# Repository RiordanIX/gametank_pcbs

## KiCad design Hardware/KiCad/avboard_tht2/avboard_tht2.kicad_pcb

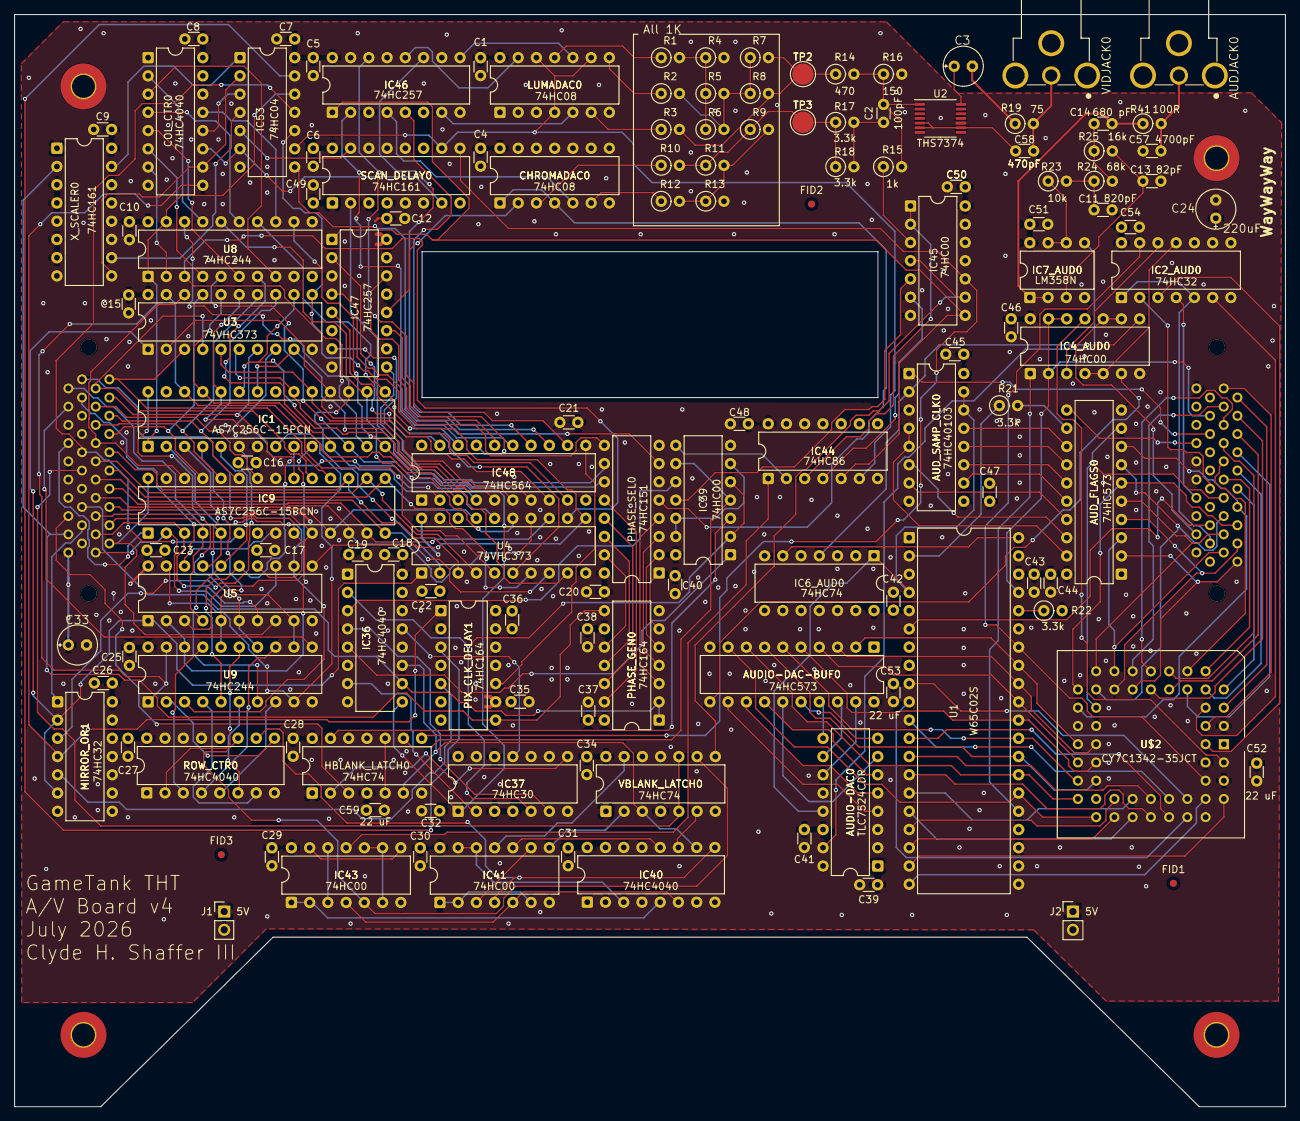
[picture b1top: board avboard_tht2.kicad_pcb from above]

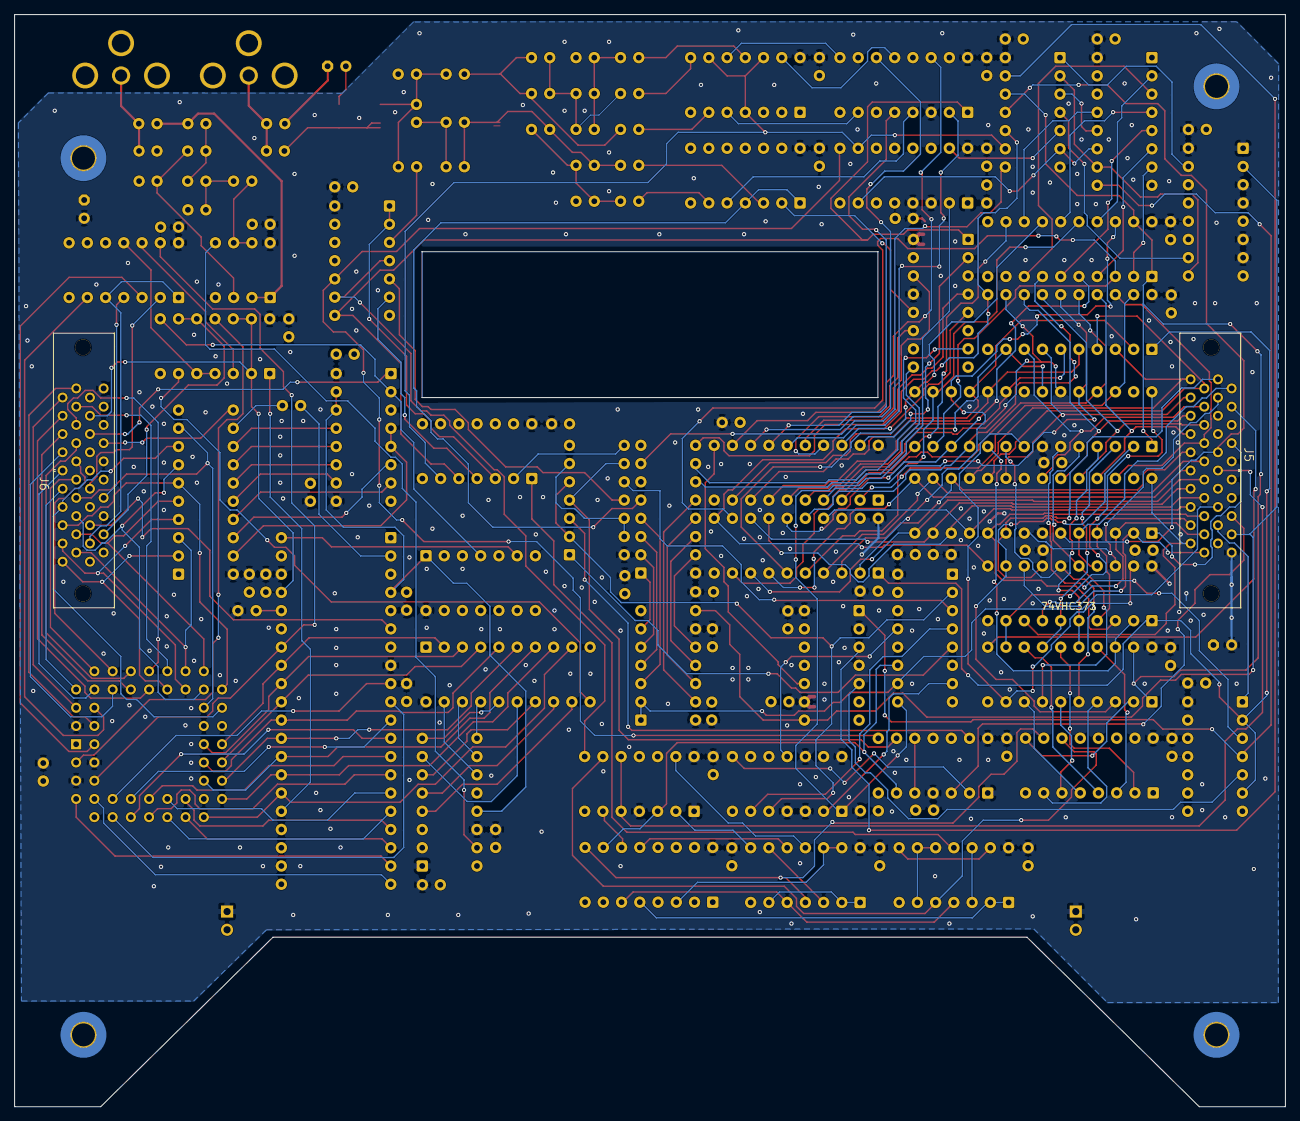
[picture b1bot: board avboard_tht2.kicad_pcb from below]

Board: 4 copper layers, 177.0 x 152.1 mm, 139 parts (2 on the bottom side), 246 nets.

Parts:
AUDIO-DAC0: TLC7524CDR; DIP-16_W7.62mm
AUDIO-DAC-BUF0: 74HC573; DIP-20_W7.62mm
AUDJACK0: RCJ-013; CUI_RCJ-014
AUD_FLAGS0: 74HC573; DIP-20_W7.62mm
AUD_SAMP_CLK0: 74HC40103; DIP-16_W7.62mm
C1, C4, C5, C6, C7, C8, C9, C10, C12, C15, C16, C17, C18, C19, C20, C21, C22, C23, C25, C26, C27, C28, C29, C30, C31, C32, C34, C35, C36, C37, C38, C39, C40, C41, C42, C43, C44, C45, C46, C47, C48, C49, C50, C51, C54: 100 nF; C_Disc_D3.0mm_W1.6mm_P2.50mm
C2: 100pF; C_Disc_D3.0mm_W1.6mm_P2.50mm
C3, C24, C33: 220uF; E2,5-6E
C11: 820pF; C_Disc_D3.0mm_W1.6mm_P2.50mm
C13: 82pF; C_Disc_D3.0mm_W1.6mm_P2.50mm
C14: 680 pF; C_Disc_D3.0mm_W1.6mm_P2.50mm
C52, C53, C59: 22 uF; C_Disc_D3.0mm_W1.6mm_P2.50mm
C57: 4700pF; C_Disc_D3.0mm_W1.6mm_P2.50mm
C58: 470pF; C_Disc_D3.0mm_W1.6mm_P2.50mm
CHROMADAC0: 74HC08; DIP-14_W7.62mm
COL_CTR0: 74HC4040; DIP-16_W7.62mm
FID1, FID2, FID3: Fiducial; Fiducial_1mm_Mask2mm
H1, H2, H3, H4: MountingHole_Pad; MountingHole_3.2mm_M3_Pad_TopBottom
HBLANK_LATCH0: 74HC74; DIP-14_W7.62mm
IC1, IC9: AS7C256C-15PCN; DIP-28_W7.62mm
IC2_AUD0: 74HC32; DIP-14_W7.62mm
IC4_AUD0, IC39, IC41, IC43, IC45: 74HC00; DIP-14_W7.62mm
IC6_AUD0: 74HC74; DIP-14_W7.62mm
IC7_AUD0: LM358N; DIP-8_W7.62mm
IC36, IC40: 74HC4040; DIP-16_W7.62mm
IC37: 74HC30; DIP-14_W7.62mm
IC44: 74HC86; DIP-14_W7.62mm
IC46, IC47: 74HC257; DIP-16_W7.62mm
IC48: 74HC564; DIP-20_W7.62mm
IC53: 74HC04; DIP-14_W7.62mm
J1, J2: 5V; PinHeader_1x02_P2.54mm_Vertical
J5: CON40_2X20_MU_TX24_JAE
J6: CON40_2X20_MU_TX25_JAE
LUMADAC0: 74HC08; DIP-14_W7.62mm
MIRROR_OR1: 74HC32; DIP-14_W7.62mm
PHASE_GEN0: 74HC164; DIP-14_W7.62mm
PHASE_SEL0: 74HC151; DIP-16_W7.62mm
PIX_CLK_DELAY1: 74HC164; DIP-14_W7.62mm
R1, R2, R3, R4, R5, R6, R7, R8, R9, R10, R11, R12, R13, R15: 1k; R_Axial_DIN0207_L6.3mm_D2.5mm_P2.54mm_Vertical
R14: 470; R_Axial_DIN0207_L6.3mm_D2.5mm_P2.54mm_Vertical
R16: 150; R_Axial_DIN0207_L6.3mm_D2.5mm_P2.54mm_Vertical
R17, R18, R21, R22: 3.3k; R_Axial_DIN0207_L6.3mm_D2.5mm_P2.54mm_Vertical
R19: 75; R_Axial_DIN0207_L6.3mm_D2.5mm_P2.54mm_Vertical
R23: 10k; R_Axial_DIN0207_L6.3mm_D2.5mm_P2.54mm_Vertical
R24: 68k; R_Axial_DIN0207_L6.3mm_D2.5mm_P2.54mm_Vertical
R25: 16k; R_Axial_DIN0207_L6.3mm_D2.5mm_P2.54mm_Vertical
R41: 100R; R_Axial_DIN0207_L6.3mm_D2.5mm_P2.54mm_Vertical
ROW_CTR0: 74HC4040; DIP-16_W7.62mm
SCAN_DELAY0: 74HC161; DIP-16_W7.62mm
TP2, TP3: TestPoint_Pad_D3.0mm
U1: W65C02S; DIP-40_W15.24mm
U2: THS7374; TSSOP-14_4.4x5mm_P0.65mm
U3, U4, U5: 74VHC373; DIP-20_W7.62mm
U8, U9: 74HC244; DIP-20_W7.62mm
U$2: CY7C1342-35JCT; PLCC-52_THT-Socket
VBLANK_LATCH0: 74HC74; DIP-14_W7.62mm
VIDJACK0: COMPOSITE; CUI_RCJ-014
X_SCALER0: 74HC161; DIP-16_W7.62mm

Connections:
/Audio Coprocessor/AA0: U1.9 (A0), U$2.45 (AR0)
/Audio Coprocessor/AA1: U1.10 (A1), U$2.44 (AR1)
/Audio Coprocessor/AA2: U1.11 (A2), U$2.43 (AR2)
/Audio Coprocessor/AA3: U1.12 (A3), U$2.42 (AR3)
/Audio Coprocessor/AA4: U1.13 (A4), U$2.41 (AR4)
/Audio Coprocessor/AA5: U1.14 (A5), U$2.40 (AR5)
/Audio Coprocessor/AA6: U1.15 (A6), U$2.39 (AR6)
/Audio Coprocessor/AA7: U1.16 (A7), U$2.38 (AR7)
/Audio Coprocessor/AA8: U1.17 (A8), U$2.37 (AR8)
/Audio Coprocessor/AA9: U1.18 (A9), U$2.36 (AR9)
/Audio Coprocessor/AA10: U1.19 (A10), U$2.47 (AR10)
/Audio Coprocessor/AA11: U1.20 (A11), U$2.48 (AR11)
/Audio Coprocessor/AA15: IC4_AUD0.1 (I0), U1.25 (A15)
/Audio Coprocessor/AD0: AUDIO-DAC-BUF0.2 (1D), U1.33 (D0), U$2.27 (DR0)
/Audio Coprocessor/AD1: AUDIO-DAC-BUF0.3 (2D), U1.32 (D1), U$2.28 (DR1)
/Audio Coprocessor/AD2: AUDIO-DAC-BUF0.4 (3D), U1.31 (D2), U$2.29 (DR2)
/Audio Coprocessor/AD3: AUDIO-DAC-BUF0.5 (4D), U1.30 (D3), U$2.30 (DR3)
/Audio Coprocessor/AD4: AUDIO-DAC-BUF0.6 (5D), U1.29 (D4), U$2.31 (DR4)
/Audio Coprocessor/AD5: AUDIO-DAC-BUF0.7 (6D), U1.28 (D5), U$2.32 (DR5)
/Audio Coprocessor/AD6: AUDIO-DAC-BUF0.8 (7D), U1.27 (D6), U$2.33 (DR6)
/Audio Coprocessor/AD7: AUDIO-DAC-BUF0.9 (8D), U1.26 (D7), U$2.34 (DR7)
/Audio Coprocessor/AR/~WB: IC2_AUD0.13 (I1), U1.34 (R/WB), U$2.50 (R/_WR)
/Audio Coprocessor/AUDIO_RDY: AUD_FLAGS0.12 (8Q), R21.2
/Audio Coprocessor/AUD_REG0: IC4_AUD0.9 (I0), IC4_AUD0.10 (I1), J6.17
/Audio Coprocessor/AUD_REG6: AUD_FLAGS0.11 (C), J6.7
/Audio Coprocessor/CLK3_5_AUD: AUD_SAMP_CLK0.1 (CP), J6.6
/Audio Coprocessor/CLK14_AUD: IC4_AUD0.2 (I1), IC4_AUD0.12 (I0), IC4_AUD0.13 (I1), J6.4, U1.37 (PH0-IN)
/Audio Coprocessor/DAC_SELECT: AUDIO-DAC-BUF0.11 (C), IC4_AUD0.6 (O)
/Audio Coprocessor/SysA0: J6.32, U$2.7 (AL0)
/Audio Coprocessor/SysA1: J6.31, U$2.8 (AL1)
/Audio Coprocessor/SysA2: J6.30, U$2.9 (AL2)
/Audio Coprocessor/SysA3: J6.29, U$2.10 (AL3)
/Audio Coprocessor/SysA4: J6.28, U$2.11 (AL4)
/Audio Coprocessor/SysA5: J6.27, U$2.12 (AL5)
/Audio Coprocessor/SysA6: J6.26, U$2.13 (AL6)
/Audio Coprocessor/SysA7: J6.25, U$2.14 (AL7)
/Audio Coprocessor/SysA8: J6.24, U$2.15 (AL8)
/Audio Coprocessor/SysA9: J6.23, U$2.16 (AL9)
/Audio Coprocessor/SysA10: J6.22, U$2.5 (AL10)
/Audio Coprocessor/SysA11: J6.21, U$2.4 (AL11)
/Audio Coprocessor/SysD0: AUD_FLAGS0.2 (1D), J6.40, U$2.17 (DL0)
/Audio Coprocessor/SysD1: AUD_FLAGS0.3 (2D), J6.39, U$2.18 (DL1)
/Audio Coprocessor/SysD2: AUD_FLAGS0.4 (3D), J6.38, U$2.19 (DL2)
/Audio Coprocessor/SysD3: AUD_FLAGS0.5 (4D), J6.37, U$2.20 (DL3)
/Audio Coprocessor/SysD4: AUD_FLAGS0.6 (5D), J6.36, U$2.21 (DL4)
/Audio Coprocessor/SysD5: AUD_FLAGS0.7 (6D), J6.35, U$2.22 (DL5)
/Audio Coprocessor/SysD6: AUD_FLAGS0.8 (7D), J6.34, U$2.23 (DL6)
/Audio Coprocessor/SysD7: AUD_FLAGS0.9 (8D), J6.33, U$2.24 (DL7)
/Audio Coprocessor/~AUDIO_IRQ: AUDIO-DAC0.13 (~WR), AUD_SAMP_CLK0.14 (TC), AUD_SAMP_CLK0.15 (PE), IC6_AUD0.1 (CLR), U1.4 (IRQB)
/Audio Coprocessor/~AUDIO_NMI: J6.16, U1.6 (NMIB)
/Audio Coprocessor/~AUDIO_RESET: AUD_SAMP_CLK0.2 (MR), IC4_AUD0.8 (O), IC6_AUD0.4 (PRE)
/Audio Coprocessor/~RE2: IC2_AUD0.4 (I0), J6.13
/Audio Coprocessor/~WAV_SEL: IC2_AUD0.1 (I0), IC2_AUD0.5 (I1), J6.18
/Audio Coprocessor/~WE2: IC2_AUD0.2 (I1), J6.12
/Composite Video Generator/1V: IC40.9 (Q1), IC41.4 (I0), ROW_CTR0.10 (P1)
/Composite Video Generator/2H: IC36.9 (Q1), IC37.1 (I0), SCAN_DELAY0.2 (CLK)
/Composite Video Generator/4H: IC36.7 (Q2), IC37.2 (I1)
/Composite Video Generator/4V: IC40.6 (Q3), IC41.5 (I1), IC43.4 (I0)
/Composite Video Generator/8V: IC40.5 (Q4), IC43.1 (I0), IC43.2 (I1)
/Composite Video Generator/16H: IC36.5 (Q4), IC39.1 (I0)
/Composite Video Generator/16V: IC40.3 (Q5), IC41.12 (I0), IC41.13 (I1)
/Composite Video Generator/32H: IC36.3 (Q5), IC39.10 (I1)
/Composite Video Generator/64H: IC36.2 (Q6), IC37.5 (I4), IC39.2 (I1), IC39.5 (I1)
/Composite Video Generator/128H: IC36.4 (Q7), IC37.6 (I5)
/Composite Video Generator/256H: IC36.13 (Q8), IC37.11 (I6)
/Composite Video Generator/256V: IC40.12 (Q9), IC41.10 (I1)
/Composite Video Generator/BURST: IC44.5 (I1), IC45.8 (O), IC46.1 (~A/B), IC47.1 (~A/B)
/Composite Video Generator/CHROMACARRIER: R9.1, R10.2, R11.1, R17.1, R18.1, TP3.1 (1_1)
/Composite Video Generator/CLK3_5: IC36.10 (P1), J5.6, PHASE_GEN0.1 (A), PHASE_GEN0.2 (B)
/Composite Video Generator/CLK7: HBLANK_LATCH0.3 (CLK), J5.5
/Composite Video Generator/CLK14: J5.4, MIRROR_OR1.1 (I0)
/Composite Video Generator/CLK28: J5.3, PHASE_GEN0.8 (CLK), PIX_CLK_DELAY1.8 (CLK), X_SCALER0.2 (CLK)
/Composite Video Generator/CSYNC: IC45.3 (O), R15.1
/Composite Video Generator/HBLANK: HBLANK_LATCH0.9 (Q), IC39.4 (I0), IC39.9 (I0)
/Composite Video Generator/HRESET: HBLANK_LATCH0.6 (~Q), IC36.11 (RES), IC40.10 (P1), VBLANK_LATCH0.3 (CLK)
/Composite Video Generator/HUE0: IC47.9 (3Y), PHASE_SEL0.11 (A)
/Composite Video Generator/HUE1: IC47.7 (2Y), PHASE_SEL0.10 (B)
/Composite Video Generator/HUE2: IC47.4 (1Y), PHASE_SEL0.9 (C)
/Composite Video Generator/LUM0: IC46.12 (4Y), LUMADAC0.13 (I1)
/Composite Video Generator/LUM1: IC46.9 (3Y), LUMADAC0.10 (I1)
/Composite Video Generator/LUM2: IC46.7 (2Y), LUMADAC0.5 (I1)
/Composite Video Generator/LUMA: R3.2, R7.2, R8.2, R14.1, TP2.1 (1_1)
/Composite Video Generator/PICTURE-ENABLE: IC44.6 (O), IC53.9 (I), LUMADAC0.4 (I0), LUMADAC0.9 (I0), LUMADAC0.12 (I0), SCAN_DELAY0.10 (ENT)
/Composite Video Generator/PIXCLK: COL_CTR0.9 (Q1), MIRROR_OR1.4 (I0), PIX_CLK_DELAY1.1 (A)
/Composite Video Generator/PIXCLK_PhaseC: MIRROR_OR1.5 (I1), PIX_CLK_DELAY1.5 (QC)
/Composite Video Generator/PIXLATCH: IC48.11 (CLK), PIX_CLK_DELAY1.10 (QE)
/Composite Video Generator/PIXLOAD: IC53.13 (I), PIX_CLK_DELAY1.3 (QA)
/Composite Video Generator/ROW_COMPLETE: COL_CTR0.12 (Q9), IC53.3 (I)
/Composite Video Generator/SAT0: CHROMADAC0.5 (I1), IC46.4 (1Y)
/Composite Video Generator/SAT1: CHROMADAC0.2 (I1), IC47.12 (4Y)
/Composite Video Generator/VBLANK: IC43.5 (I1), ROW_CTR0.11 (RES), VBLANK_LATCH0.9 (Q)
/Composite Video Generator/VRESET: IC40.11 (RES), VBLANK_LATCH0.6 (~Q)
/Composite Video Generator/VWE: IC53.10 (O), U3.11 (LE), U4.11 (LE), U5.11 (LE)
/Composite Video Generator/XCLK: COL_CTR0.10 (P1), IC53.2 (O), X_SCALER0.9 (LD)
/Composite Video Generator/XRESET: COL_CTR0.11 (RES), IC53.6 (O), SCAN_DELAY0.7 (ENP)
/Composite Video Generator/~8V: IC43.3 (O), IC43.12 (I0)
/Composite Video Generator/~HBLANK: HBLANK_LATCH0.8 (~Q), IC45.10 (I1), SCAN_DELAY0.9 (LD)
/Composite Video Generator/~HRESET: HBLANK_LATCH0.5 (Q), HBLANK_LATCH0.10 (PRE)
/Composite Video Generator/~HSYNC: IC39.8 (O), IC44.2 (I1)
/Composite Video Generator/~MirrorLoad: MIRROR_OR1.2 (I1), MIRROR_OR1.6 (O), U3.1 (OE), U4.1 (OE), U5.1 (OE)
/Composite Video Generator/~MirrorWE: IC1.6 (~WE), MIRROR_OR1.3 (O)
/Composite Video Generator/~PICTURE-ENABLE: IC53.8 (O), PHASE_SEL0.7 (G)
/Composite Video Generator/~PIXLOAD: IC1.1 (~OE), IC53.12 (O), U8.1 (1OE), U8.19 (2OE), U9.1 (1OE), U9.19 (2OE)
/Composite Video Generator/~VBLANK: IC45.4 (I0), IC45.9 (I0), VBLANK_LATCH0.8 (~Q)
/Composite Video Generator/~VOE: IC9.1 (~OE), J5.13
/Composite Video Generator/~VRESET: J5.10, VBLANK_LATCH0.5 (Q), VBLANK_LATCH0.10 (PRE)
/Composite Video Generator/~VSYNC: IC43.11 (O), IC44.1 (I0)
/Composite Video Generator/~VWE: IC9.6 (~WE), IC53.11 (I), J5.12
GND: AUDIO-DAC0.2 (OUT2), AUDIO-DAC0.3 (GND), AUDIO-DAC0.12 (~CS), AUDIO-DAC-BUF0.1 (OC), AUDIO-DAC-BUF0.10 (GND), AUDJACK0.1A (1), AUDJACK0.1B (1), AUDJACK0.1C (1), AUD_FLAGS0.1 (OC), AUD_FLAGS0.10 (GND), AUD_SAMP_CLK0.3 (TE), AUD_SAMP_CLK0.8 (GND), C1.2, C4.2, C5.2, C6.2, C7.2, C8.2, C9.2, C10.2, C11.1, C12.2, C13.1, C15.2, C16.2, C17.2, C18.2, C19.2, C20.2, C21.2, C22.2, C23.2, C24.-, C25.2, C26.2, C27.2, C28.2, C29.2, C30.2, C31.2, C32.2, C33.-, C34.2, C35.2, C36.2, C37.2, C38.2, C39.2, C40.2, C41.2, C42.2, C43.2, C44.2, C45.2, C46.2, C47.2, C48.2, C49.2, C50.2, C51.2, C52.2, C53.2, C54.2, C57.2, C58.2, C59.2, CHROMADAC0.7 (GND), CHROMADAC0.9 (I0), CHROMADAC0.10 (I1), CHROMADAC0.12 (I0), CHROMADAC0.13 (I1), COL_CTR0.8 (VSS), H1.1 (1_1), H2.1 (1_1), H3.1 (1_1), H4.1 (1_1), HBLANK_LATCH0.7 (GND), HBLANK_LATCH0.11 (CLK), HBLANK_LATCH0.12 (D), IC1.21 (GND), IC1.27 (~CE), IC2_AUD0.7 (GND), IC4_AUD0.7 (GND), IC6_AUD0.3 (CLK), IC6_AUD0.7 (GND), IC7_AUD0.4 (V-), IC9.21 (GND), IC9.27 (~CE), IC36.8 (VSS), IC37.7 (GND), IC39.7 (GND), IC40.8 (VSS), IC41.7 (GND), IC43.7 (GND), IC44.7 (GND), IC45.7 (GND), IC46.6 (2B), IC46.8 (GND), IC46.10 (3B), IC46.13 (4B), IC46.15 (G), IC47.3 (1B), IC47.6 (2B), IC47.8 (GND), IC47.10 (3B), IC47.15 (G), IC48.1 (OC), IC48.10 (GND), IC53.7 (GND), J1.2, J2.2, J5.2, J5.7, J5.8, J5.9, J5.11, J5.14, J5.15, J5.16, J6.2, J6.8, J6.19, J6.20, LUMADAC0.1 (I0), LUMADAC0.2 (I1), LUMADAC0.7 (GND), MIRROR_OR1.7 (GND), PHASE_GEN0.7 (GND), PHASE_SEL0.8 (GND), PIX_CLK_DELAY1.7 (GND), R4.2, R13.2, R16.2, ROW_CTR0.8 (VSS), SCAN_DELAY0.5 (C), SCAN_DELAY0.6 (D), SCAN_DELAY0.8 (GND), U1.21 (VSS), U2.5 (GND), U2.6 (DISABLE), U2.9 (BYPASS), U3.10 (GND), U4.10 (GND), U4.18 (D7), U5.10 (GND), U8.10 (GND), U8.11 (2A3), U9.10 (GND), U$2.1 (_CEL), U$2.26 (GND), U$2.46 (_OER), VBLANK_LATCH0.7 (GND), VBLANK_LATCH0.11 (CLK), VBLANK_LATCH0.12 (D), VIDJACK0.1A (1), VIDJACK0.1B (1), VIDJACK0.1C (1), X_SCALER0.5 (C), X_SCALER0.8 (GND)
MA0: IC1.17 (A0), U4.2 (O0), U8.18 (1Y0)
MA1: IC1.16 (A1), U4.5 (O1), U8.16 (1Y1)
MA2: IC1.15 (A2), U4.6 (O2), U8.14 (1Y2)
MA3: IC1.14 (A3), U4.9 (O3), U8.12 (1Y3)
MA4: IC1.13 (A4), U4.12 (O4), U8.3 (2Y0)
MA5: IC1.12 (A5), U4.15 (O5), U8.5 (2Y1)
MA6: IC1.11 (A6), U4.16 (O6), U8.7 (2Y2)
MA7: IC1.10 (A7), U5.2 (O0), U9.18 (1Y0)
MA8: IC1.4 (A8), U5.5 (O1), U9.16 (1Y1)
MA9: IC1.3 (A9), U5.6 (O2), U9.14 (1Y2)
MA10: IC1.28 (A10), U5.9 (O3), U9.12 (1Y3)
MA11: IC1.2 (A11), U5.12 (O4), U9.3 (2Y0)
MA12: IC1.9 (A12), U5.15 (O5), U9.5 (2Y1)
MA13: IC1.5 (A13), U5.16 (O6), U9.7 (2Y2)
MA14: IC1.8 (A14), U5.19 (O7), U9.9 (2Y3)
unnamed: AUDIO-DAC0.15 (VREF), IC7_AUD0.5 (+IN)
unnamed: AUDIO-DAC0.11 (D0), AUDIO-DAC-BUF0.19 (1Q)
unnamed: AUDIO-DAC0.10 (D1), AUDIO-DAC-BUF0.18 (2Q)
unnamed: AUDIO-DAC0.9 (D2), AUDIO-DAC-BUF0.17 (3Q)
unnamed: AUDIO-DAC0.8 (D3), AUDIO-DAC-BUF0.16 (4Q)
unnamed: AUDIO-DAC0.7 (D4), AUDIO-DAC-BUF0.15 (5Q)
unnamed: AUDIO-DAC0.6 (D5), AUDIO-DAC-BUF0.14 (6Q)
unnamed: AUDIO-DAC0.5 (D6), AUDIO-DAC-BUF0.13 (7Q)
unnamed: AUDIO-DAC0.4 (D7), AUDIO-DAC-BUF0.12 (8Q)
unnamed: AUDJACK0.2, C57.1, R41.2
unnamed: AUD_FLAGS0.19 (1Q), AUD_SAMP_CLK0.4 (P0), AUD_SAMP_CLK0.5 (P1)
unnamed: AUD_FLAGS0.18 (2Q), AUD_SAMP_CLK0.6 (P2)
unnamed: AUD_FLAGS0.17 (3Q), AUD_SAMP_CLK0.7 (P3)
unnamed: AUD_FLAGS0.16 (4Q), AUD_SAMP_CLK0.10 (P4)
unnamed: AUD_FLAGS0.15 (5Q), AUD_SAMP_CLK0.11 (P5)
unnamed: AUD_FLAGS0.14 (6Q), AUD_SAMP_CLK0.12 (P6)
unnamed: AUD_FLAGS0.13 (7Q), AUD_SAMP_CLK0.13 (P7)
unnamed: C2.1, R17.2, R18.2
unnamed: C3.-, R19.1
unnamed: C11.2, R23.2, R24.1
unnamed: C14.1, R24.2, R25.1
unnamed: C58.1, R19.2, VIDJACK0.2
unnamed: CHROMADAC0.1 (I0), CHROMADAC0.4 (I0), PHASE_SEL0.5 (Y)
unnamed: CHROMADAC0.3 (O), R10.1
unnamed: CHROMADAC0.6 (O), R12.1
unnamed: HBLANK_LATCH0.2 (D), IC37.8 (O)
unnamed: HBLANK_LATCH0.13 (CLR), IC39.3 (O)
unnamed: IC2_AUD0.3 (O), U$2.2 (R/_WL)
unnamed: IC2_AUD0.6 (O), U$2.6 (_OEL)
unnamed: IC2_AUD0.12 (I0), IC4_AUD0.3 (O)
unnamed: IC2_AUD0.11 (O), IC4_AUD0.4 (I0), IC4_AUD0.5 (I1)
unnamed: IC4_AUD0.11 (O), U$2.51 (_CER)
unnamed: IC6_AUD0.6 (~Q), U1.40 (RESB)
unnamed: C13.2, IC7_AUD0.3 (+IN), R25.2
unnamed: C14.2, IC7_AUD0.1 (OUT), IC7_AUD0.2 (-IN), R41.1
unnamed: IC7_AUD0.6 (-IN), IC7_AUD0.7 (OUT), R23.1
unnamed: IC39.6 (O), IC39.12 (I0), IC39.13 (I1)
unnamed: IC39.11 (O), IC45.5 (I1)
unnamed: IC41.1 (I0), IC41.2 (I1), IC41.6 (O)
unnamed: IC41.3 (O), IC41.9 (I0)
unnamed: IC41.8 (O), VBLANK_LATCH0.2 (D)
unnamed: IC41.11 (O), VBLANK_LATCH0.13 (CLR)
unnamed: IC43.6 (O), IC43.9 (I0), IC43.10 (I1)
unnamed: IC43.8 (O), IC43.13 (I1)
unnamed: IC44.3 (O), IC45.1 (I0), IC45.2 (I1)
unnamed: IC44.4 (I0), IC45.6 (O)
unnamed: IC46.2 (1A), IC48.15 (5Q)
unnamed: IC46.5 (2A), IC48.14 (6Q)
unnamed: IC46.11 (3A), IC48.13 (7Q)
unnamed: IC46.14 (4A), IC48.12 (8Q)
unnamed: IC47.2 (1A), IC48.19 (1Q)
unnamed: IC47.5 (2A), IC48.18 (2Q)
unnamed: IC47.11 (3A), IC48.17 (3Q)
unnamed: IC47.14 (4A), IC48.16 (4Q)
unnamed: IC53.1 (I), X_SCALER0.15 (RCO)
unnamed: IC53.4 (O), X_SCALER0.10 (ENT)
unnamed: IC53.5 (I), SCAN_DELAY0.15 (RCO)
unnamed: LUMADAC0.6 (O), R3.1
unnamed: LUMADAC0.8 (O), R2.1
unnamed: LUMADAC0.11 (O), R1.1
unnamed: PHASE_GEN0.3 (QA), PHASE_SEL0.4 (D0)
unnamed: PHASE_GEN0.4 (QB), PHASE_SEL0.3 (D1)
unnamed: PHASE_GEN0.5 (QC), PHASE_SEL0.2 (D2)
unnamed: PHASE_GEN0.6 (QD), PHASE_SEL0.1 (D3)
unnamed: PHASE_GEN0.10 (QE), PHASE_SEL0.15 (D4)
unnamed: PHASE_GEN0.11 (QF), PHASE_SEL0.14 (D5)
unnamed: PHASE_GEN0.12 (QG), PHASE_SEL0.13 (D6)
unnamed: PHASE_GEN0.13 (QH), PHASE_SEL0.12 (D7)
unnamed: R1.2, R4.1, R5.1, R6.1
unnamed: R2.2, R5.2, R6.2, R7.1, R8.1
unnamed: R9.2, R11.2, R12.2, R13.1
unnamed: R22.1, U1.36 (BE)
unnamed: R21.1, U1.2 (RDY)
unnamed: C2.2, R14.2, R15.2, R16.1, U2.1 (CH1_IN)
unnamed: C3.+, U2.14 (CH1_OUT)
P0: IC1.18 (I/O0), IC48.9 (8D), U3.2 (O0)
P1: IC1.19 (I/O1), IC48.8 (7D), U3.5 (O1)
P2: IC1.20 (I/O2), IC48.7 (6D), U3.6 (O2)
P3: IC1.22 (I/O3), IC48.6 (5D), U3.9 (O3)
P4: IC1.23 (I/O4), IC48.5 (4D), U3.12 (O4)
P5: IC1.24 (I/O5), IC48.4 (3D), U3.15 (O5)
P6: IC1.25 (I/O6), IC48.3 (2D), U3.16 (O6)
P7: IC1.26 (I/O7), IC48.2 (1D), U3.19 (O7)
PAX0: COL_CTR0.7 (Q2), U8.2 (1A0)
PAX1: COL_CTR0.6 (Q3), U8.4 (1A1)
PAX2: COL_CTR0.5 (Q4), U8.6 (1A2)
PAX3: COL_CTR0.3 (Q5), U8.8 (1A3)
PAX4: COL_CTR0.2 (Q6), U8.17 (2A0)
PAX5: COL_CTR0.4 (Q7), U8.15 (2A1)
PAX6: COL_CTR0.13 (Q8), U8.13 (2A2)
PAY0: ROW_CTR0.9 (Q1), U9.2 (1A0)
PAY1: ROW_CTR0.7 (Q2), U9.4 (1A1)
PAY2: ROW_CTR0.6 (Q3), U9.6 (1A2)
PAY3: ROW_CTR0.5 (Q4), U9.8 (1A3)
PAY4: ROW_CTR0.3 (Q5), U9.17 (2A0)
PAY5: ROW_CTR0.2 (Q6), U9.15 (2A1)
PAY6: ROW_CTR0.4 (Q7), U9.13 (2A2)
VA0: IC9.17 (A0), J5.32, U4.3 (D0)
VA1: IC9.16 (A1), J5.31, U4.4 (D1)
VA2: IC9.15 (A2), J5.30, U4.7 (D2)
VA3: IC9.14 (A3), J5.29, U4.8 (D3)
VA4: IC9.13 (A4), J5.28, U4.13 (D4)
VA5: IC9.12 (A5), J5.27, U4.14 (D5)
VA6: IC9.11 (A6), J5.26, U4.17 (D6)
VA7: IC9.10 (A7), J5.25, U5.3 (D0)
VA8: IC9.4 (A8), J5.24, U5.4 (D1)
VA9: IC9.3 (A9), J5.23, U5.7 (D2)
VA10: IC9.28 (A10), J5.22, U5.8 (D3)
VA11: IC9.2 (A11), J5.21, U5.13 (D4)
VA12: IC9.9 (A12), J5.20, U5.14 (D5)
VA13: IC9.5 (A13), J5.19, U5.17 (D6)
VA14: IC9.8 (A14), J5.18, U5.18 (D7)
VCC: AUDIO-DAC0.1 (OUT1), AUDIO-DAC0.14 (VDD), AUDIO-DAC-BUF0.20 (VCC), AUD_FLAGS0.20 (VCC), AUD_SAMP_CLK0.9 (PL), AUD_SAMP_CLK0.16 (VCC), C1.1, C4.1, C5.1, C6.1, C7.1, C8.1, C9.1, C10.1, C12.1, C15.1, C16.1, C17.1, C18.1, C19.1, C20.1, C21.1, C22.1, C23.1, C24.+, C25.1, C26.1, C27.1, C28.1, C29.1, C30.1, C31.1, C32.1, C33.+, C34.1, C35.1, C36.1, C37.1, C38.1, C39.1, C40.1, C41.1, C42.1, C43.1, C44.1, C45.1, C46.1, C47.1, C48.1, C49.1, C50.1, C51.1, C52.1, C53.1, C54.1, C59.1, CHROMADAC0.14 (VCC), COL_CTR0.16 (VDD), HBLANK_LATCH0.1 (CLR), HBLANK_LATCH0.4 (PRE), HBLANK_LATCH0.14 (VCC), IC1.7 (VCC), IC2_AUD0.14 (VCC), IC4_AUD0.14 (VCC), IC6_AUD0.14 (VCC), IC7_AUD0.8 (V+), IC9.7 (VCC), IC36.16 (VDD), IC37.3 (I2), IC37.4 (I3), IC37.12 (I7), IC37.14 (VCC), IC39.14 (VCC), IC40.16 (VDD), IC41.14 (VCC), IC43.14 (VCC), IC44.14 (VCC), IC45.14 (VCC), IC46.3 (1B), IC46.16 (VCC), IC47.13 (4B), IC47.16 (VCC), IC48.20 (VCC), IC53.14 (VCC), J1.1, J2.1, J5.1, J6.1, LUMADAC0.14 (VCC), MIRROR_OR1.14 (VCC), PHASE_GEN0.9 (CLR), PHASE_GEN0.14 (VCC), PHASE_SEL0.16 (VCC), PIX_CLK_DELAY1.2 (B), PIX_CLK_DELAY1.9 (CLR), PIX_CLK_DELAY1.14 (VCC), R22.2, ROW_CTR0.16 (VDD), SCAN_DELAY0.1 (CLR), SCAN_DELAY0.3 (A), SCAN_DELAY0.4 (B), SCAN_DELAY0.16 (VCC), U1.8 (VDD), U1.38 (SOB), U2.10 (V_{S+}), U3.20 (VCC), U4.20 (VCC), U5.20 (VCC), U8.20 (VCC), U9.20 (VCC), U$2.3 (_SEML), U$2.49 (_SEMR), U$2.52 (VCC), VBLANK_LATCH0.1 (CLR), VBLANK_LATCH0.4 (PRE), VBLANK_LATCH0.14 (VCC), X_SCALER0.1 (CLR), X_SCALER0.3 (A), X_SCALER0.4 (B), X_SCALER0.6 (D), X_SCALER0.7 (ENP), X_SCALER0.16 (VCC)
VD0: IC9.18 (I/O0), J5.40, U3.3 (D0)
VD1: IC9.19 (I/O1), J5.39, U3.4 (D1)
VD2: IC9.20 (I/O2), J5.38, U3.7 (D2)
VD3: IC9.22 (I/O3), J5.37, U3.8 (D3)
VD4: IC9.23 (I/O4), J5.36, U3.13 (D4)
VD5: IC9.24 (I/O5), J5.35, U3.14 (D5)
VD6: IC9.25 (I/O6), J5.34, U3.17 (D6)
VD7: IC9.26 (I/O7), J5.33, U3.18 (D7)
VIDPAGE: J5.17, U9.11 (2A3)

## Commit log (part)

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2022-08-02 Add schematics in image form
2022-08-04 Upload PDF schematics
2022-08-27 Replacement PCB for THS7374 module
2022-08-30 add SMD oscillator to library and fix GRAM power connections
2022-08-31 fix ACP control lines (in schematic)
2022-09-03 Fix flipped SMD oscillator
2022-09-03 Replace MUX for readregs with spare gates
2022-09-29 Catridge adapter for Sanni reader and first draft of SRAM cartridge
2022-10-05 Add chip placement guides
2022-10-09 reorg STLs and add controller model
2022-11-03 more sram cart changes
2023-01-26 Reorganize Production (gerber zips) folder
2023-03-06 upload parts lists
2023-03-06 RAM cartridge fixes
2023-08-22 upload kicad conversions and smt versions
2023-08-22 some SRAM cartridge stuff
2023-08-22 convert Power module to KiCad
2023-08-23 power board kicad smt
2023-08-23 update kicad SMT BOMs
2023-11-28 SMT edits and start of fake dual ram sketching
2024-01-04 updates to kicad smt versions
2024-08-06 manual and models and misc hardware file updates
2024-08-20 Add new flasher v3
2024-08-20 update graphics on flasher v3
2024-08-20 fix unconnected nets in flasher3
2024-08-28 add footprint for reset controller on logic board and remove READY on cartridges
2024-08-29 megaprogrammer edit
2024-09-06 controller cad files and new cart flasher
2024-09-07 flasher2 sent for prototype production
2024-09-13 fix for smt controller
2025-07-05 add media files for presentations and websites etc
2025-10-03 collect production documents for quoting
2025-10-15 replace dual ported frame buffer with mirrored single ported rams
2025-10-15 design out the 4K dualport ram
2025-10-15 connect loose unused inputs to ground
2025-10-19 add svg of console badge
2025-10-19 add gamepad svg and iconified gametank image
2025-11-24 fix composite video generator board
2025-11-24 update manf brief
2025-12-01 Add quote files for molding
2025-12-01 Add AV board version with VRAM replaced but not ARAM
2025-12-01 update box label
2026-02-22 add draft of 2M cart with center hole
2026-03-05 warped checkerboard box
2026-03-05 more random updates
2026-03-06 mailer box cutout doc
2026-03-06 tweaks to gametank box template
2026-06-20 lots of emc tweaking, not done yet
2026-06-20 packaging update
2026-06-29 EMC updates part ?/?
